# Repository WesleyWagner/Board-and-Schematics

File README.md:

# Boards and Schematics
Diretório provisório destinado ao armazenamento dos desenhos das PCB's relacionadas ao projeto SAIOT.

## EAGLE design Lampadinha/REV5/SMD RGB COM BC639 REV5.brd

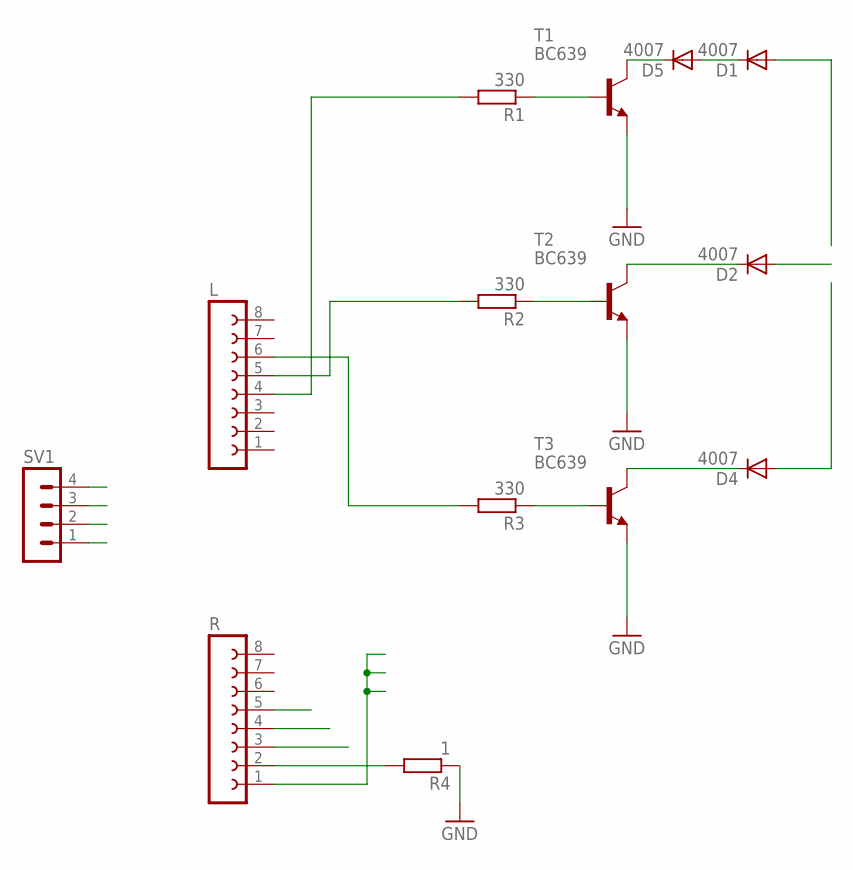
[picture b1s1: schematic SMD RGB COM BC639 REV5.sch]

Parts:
D1, D2, D4, D5: 4007; DO35-7
L: FE08-1; FE08
R: FE08-1; FE08
R1, R2, R3: 330; 0204/7
R4: 1; 0204/7
SV1: MA04-1
T1, T2, T3: BC639; TO92-ECB

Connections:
+5V: R.1, SV1.4
BB: R3.1, T3.B
BG: R2.1, T2.B
BI: L.6, R3.2
BO: D4.A, SV1.3
BR: R1.1, T1.B
GI: L.5, R2.2
GND: R4.1, T1.E, T2.E, T3.E
GNDIN: R.2, R4.2
GO: D2.A, SV1.2
unnamed: D2.C, T2.C
unnamed: D1.C, D5.A
unnamed: D5.C, T1.C
unnamed: D4.C, T3.C
RI: L.4, R1.2
RO: D1.A, SV1.1

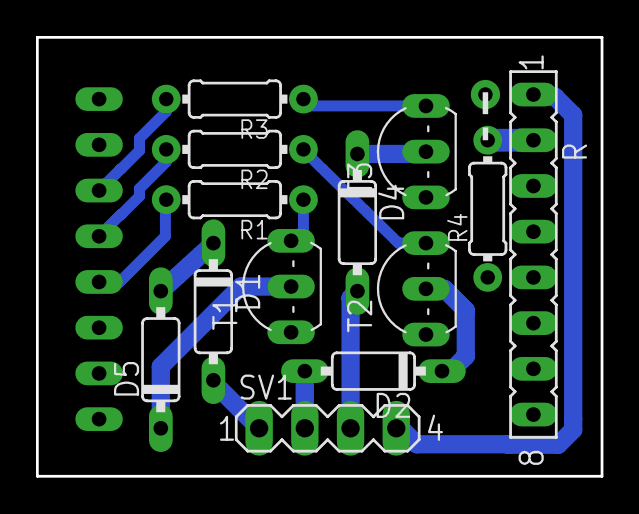
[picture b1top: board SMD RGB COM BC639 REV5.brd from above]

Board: 2 copper layers, 31.4 x 24.4 mm, 14 parts (1 on the bottom side), 16 nets.

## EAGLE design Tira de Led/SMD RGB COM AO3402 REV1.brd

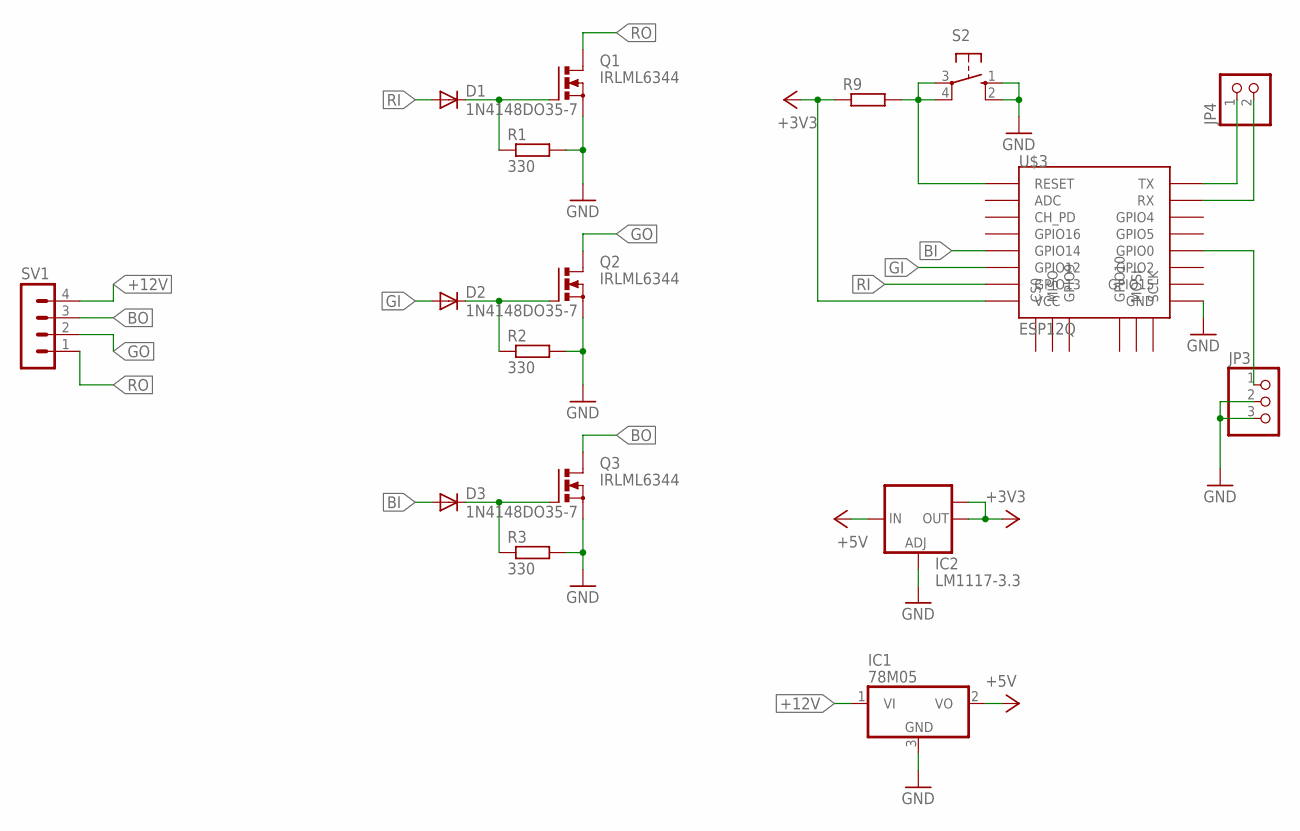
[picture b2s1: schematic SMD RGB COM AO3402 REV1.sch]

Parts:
D1, D2, D3: 1N4148DO35-7; DO35-7
IC1: 78M05; TO252
IC2: LM1117-3.3; SOT223
JP3: PINHD-1X3; 1X03
JP4: PINHD-1X2; 1X02
Q1, Q2, Q3: IRLML6344; SOT-23
R1, R2, R3: 330; 0204/7
R9: R-EU_0204/7; 0204/7
S2: 10-XX; B3F-10XX
SV1: MA04-1
U$3: ESP12Q

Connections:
+3V3: IC2.2 (OUT), IC2.TAB (OUT1), R9.1, U$3.VCC
+5V: IC1.2 (VO), IC2.3 (IN)
+12V: IC1.1 (VI), SV1.4
BB: D3.C, Q3.P1 (G), R3.1
BG: D2.C, Q2.P1 (G), R2.1
BI: D3.A, U$3.GPIO14
BO: Q3.P3 (D), SV1.3
BR: D1.C, Q1.P1 (G), R1.1
GI: D2.A, U$3.GPIO12
GND: IC1.3 (GND), IC2.1 (ADJ), JP3.2, JP3.3, Q1.P2 (S), Q2.P2 (S), Q3.P2 (S), R1.2, R2.2, R3.2, S2.1 (S), S2.2 (S1), U$3.GND
GO: Q2.P3 (D), SV1.2
unnamed: R9.2, S2.3, S2.4 (P1), U$3.RESET
unnamed: JP3.1, U$3.GPIO0
unnamed: JP4.1, U$3.TX
unnamed: JP4.2, U$3.RX
RI: D1.A, U$3.GPIO13
RO: Q1.P3 (D), SV1.1

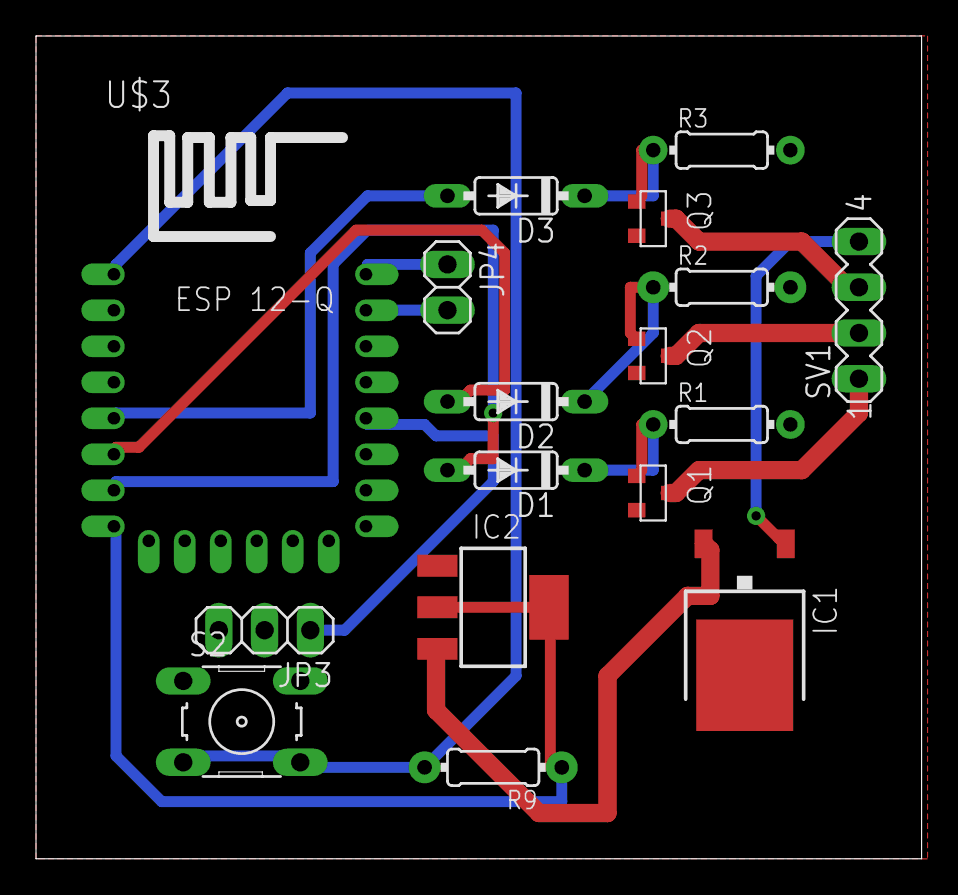
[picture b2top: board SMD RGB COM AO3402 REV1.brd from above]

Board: 2 copper layers, 49.2 x 45.7 mm, 17 parts (0 on the bottom side), 17 nets.
